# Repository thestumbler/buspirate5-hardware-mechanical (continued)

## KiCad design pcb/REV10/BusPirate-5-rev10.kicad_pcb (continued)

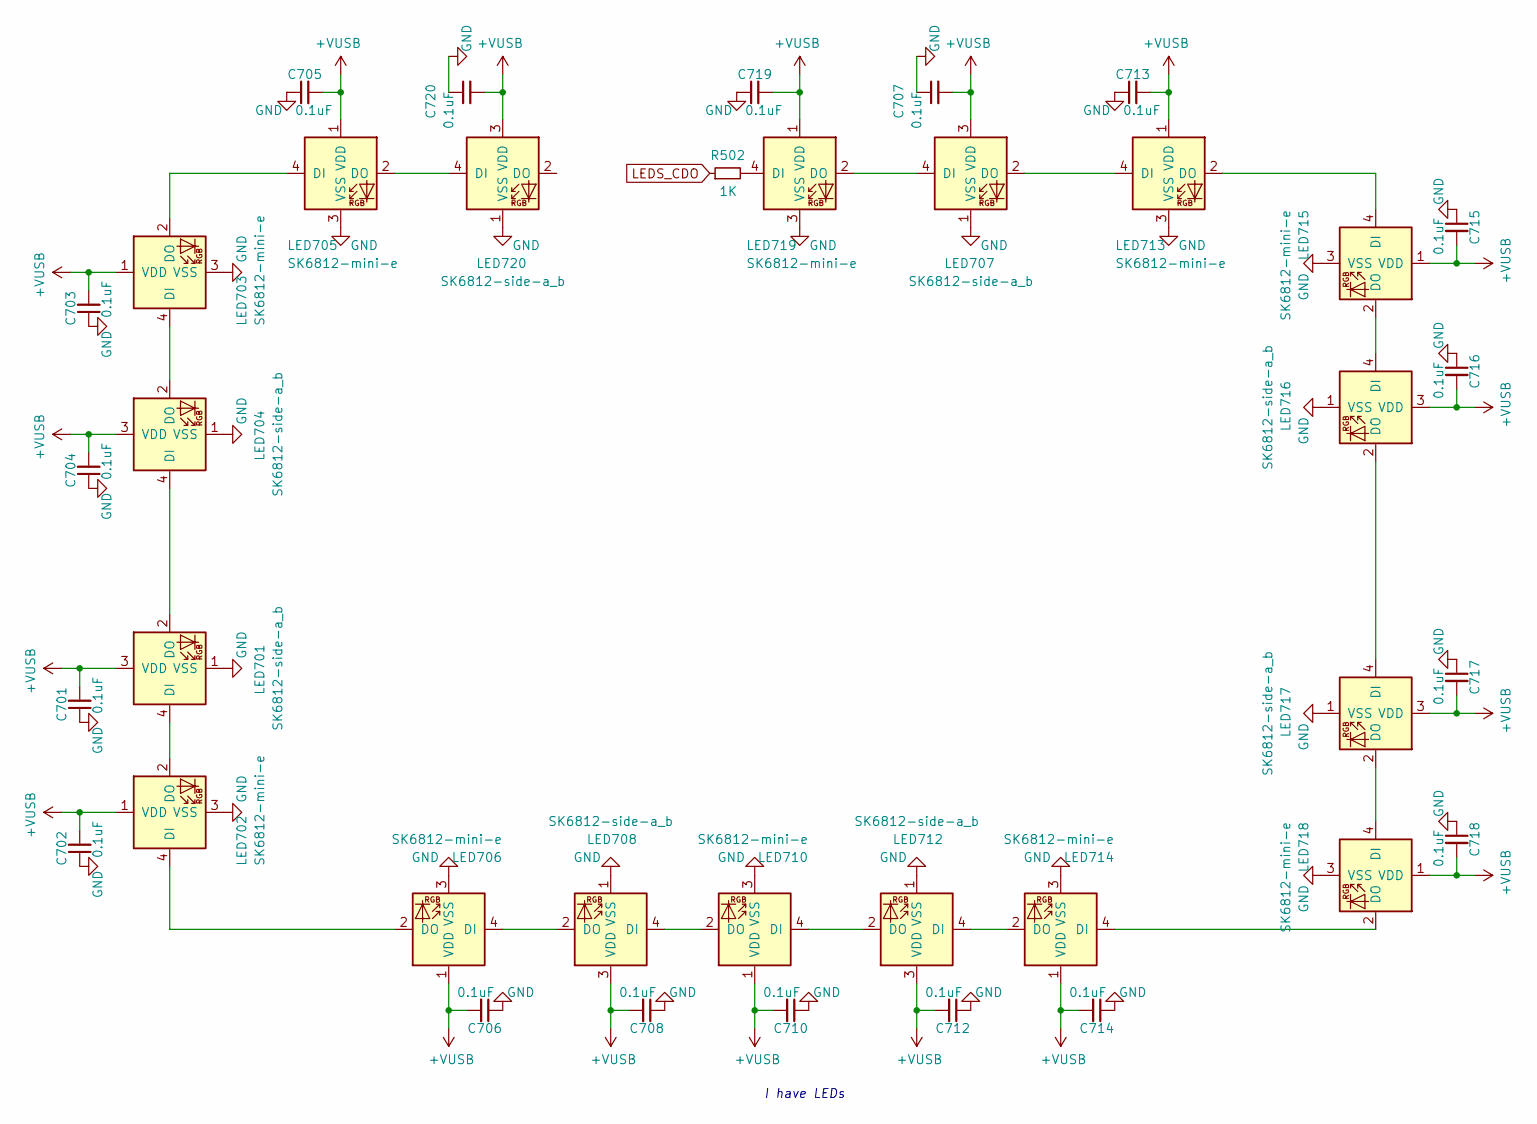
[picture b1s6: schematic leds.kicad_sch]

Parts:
C701, C702, C703, C704, C705, C706, C707, C708, C710, C712, C713, C714, C715, C716, C717, C718, C719, C720: 0.1uF; C_0402_1005Metric
LED701, LED704, LED707, LED708, LED712, LED716, LED717, LED720: SK6812-side-a_b
LED702, LED703, LED705, LED706, LED710, LED713, LED714, LED715, LED718, LED719: SK6812-mini-e
R502: 1K; R_0402_1005Metric

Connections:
+VUSB: C701.2, C702.2, C703.2, C704.2, C705.2, C706.2, C707.2, C708.2, C710.2, C712.2, C713.2, C714.2, C715.2, C716.2, C717.2, C718.2, C719.2, C720.2, LED701.3 (VDD), LED702.1 (VDD), LED703.1 (VDD), LED704.3 (VDD), LED705.1 (VDD), LED706.1 (VDD), LED707.3 (VDD), LED708.3 (VDD), LED710.1 (VDD), LED712.3 (VDD), LED713.1 (VDD), LED714.1 (VDD), LED715.1 (VDD), LED716.3 (VDD), LED717.3 (VDD), LED718.1 (VDD), LED719.1 (VDD), LED720.3 (VDD); also elsewhere on the board
GND: C701.1, C702.1, C703.1, C704.1, C705.1, C706.1, C707.1, C708.1, C710.1, C712.1, C713.1, C714.1, C715.1, C716.1, C717.1, C718.1, C719.1, C720.1, LED701.1 (VSS), LED702.3 (VSS), LED703.3 (VSS), LED704.1 (VSS), LED705.3 (VSS), LED706.3 (VSS), LED707.1 (VSS), LED708.1 (VSS), LED710.3 (VSS), LED712.1 (VSS), LED713.3 (VSS), LED714.3 (VSS), LED715.3 (VSS), LED716.1 (VSS), LED717.1 (VSS), LED718.3 (VSS), LED719.3 (VSS), LED720.1 (VSS); also elsewhere on the board
LEDS_CDO: R502.1; also elsewhere on the board
unnamed: LED701.4 (DI), LED702.2 (DO)
unnamed: LED701.2 (DO), LED704.4 (DI)
unnamed: LED702.4 (DI), LED706.2 (DO)
unnamed: LED703.4 (DI), LED704.2 (DO)
unnamed: LED703.2 (DO), LED705.4 (DI)
unnamed: LED705.2 (DO), LED720.4 (DI)
unnamed: LED706.4 (DI), LED708.2 (DO)
unnamed: LED707.4 (DI), LED719.2 (DO)
unnamed: LED707.2 (DO), LED713.4 (DI)
unnamed: LED708.4 (DI), LED710.2 (DO)
unnamed: LED710.4 (DI), LED712.2 (DO)
unnamed: LED712.4 (DI), LED714.2 (DO)
unnamed: LED713.2 (DO), LED715.4 (DI)
unnamed: LED714.4 (DI), LED718.2 (DO)
unnamed: LED715.2 (DO), LED716.4 (DI)
unnamed: LED716.2 (DO), LED717.4 (DI)
unnamed: LED717.2 (DO), LED718.4 (DI)
unnamed: LED719.4 (DI), R502.2

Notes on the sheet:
I have LEDs

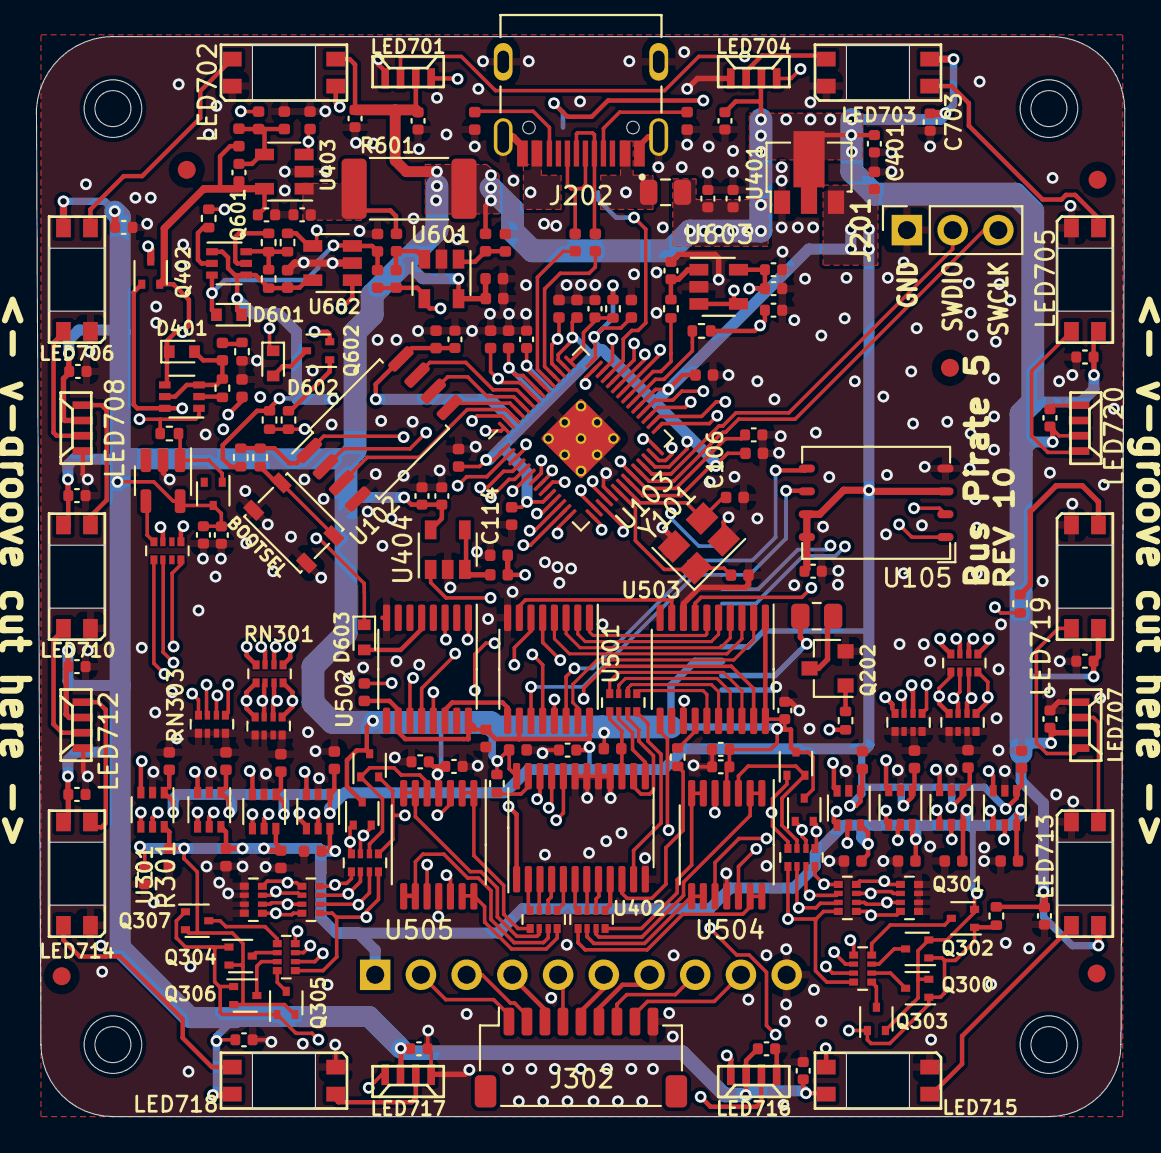
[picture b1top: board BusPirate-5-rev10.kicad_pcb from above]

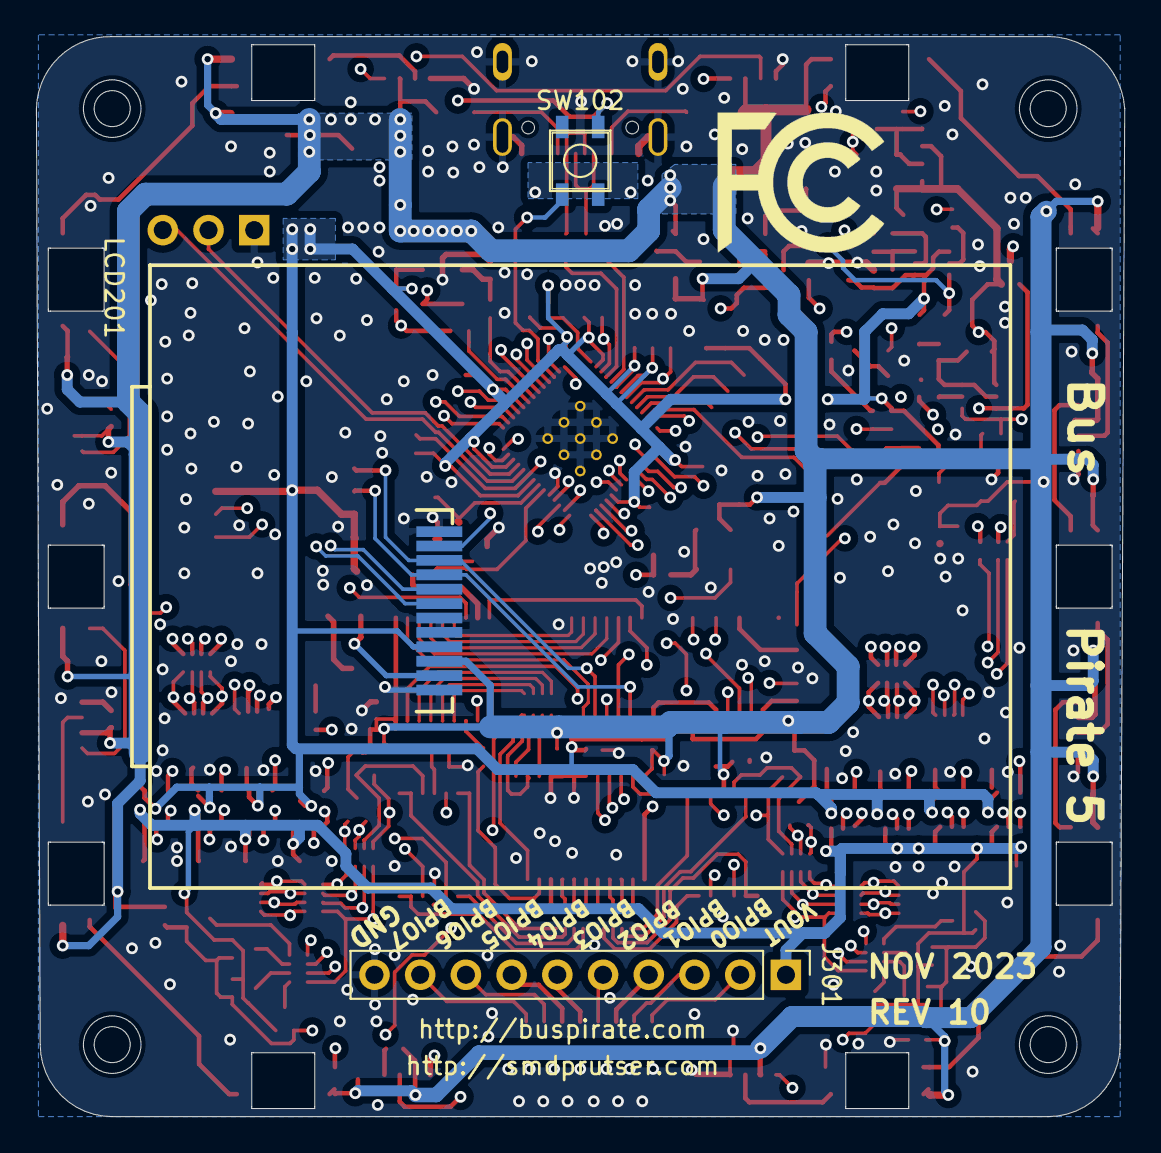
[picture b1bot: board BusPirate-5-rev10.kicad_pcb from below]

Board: 4 copper layers, 60.5 x 60.0 mm, 220 parts (4 on the bottom side), 183 nets.

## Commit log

2024-10-19 making chris branch
2024-10-22 almost wrapped up
2024-10-25 clean up directory names
2024-10-25 removed unrelated directories
2024-10-25 making readme comments
2024-10-25 fixed image path
2024-10-25 removed unnecessary PCB versions
